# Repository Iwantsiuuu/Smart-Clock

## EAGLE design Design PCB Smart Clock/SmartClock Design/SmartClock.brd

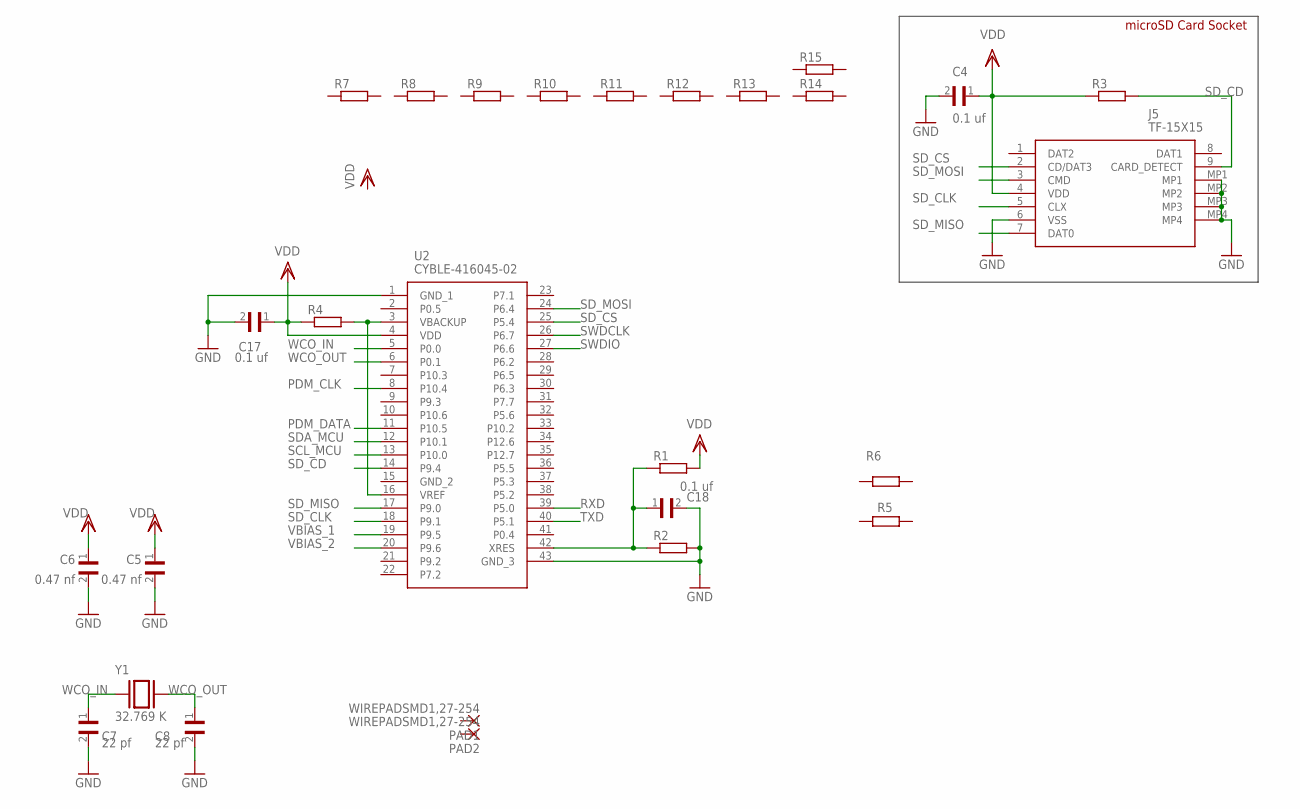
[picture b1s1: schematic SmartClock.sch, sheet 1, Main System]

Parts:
C4, C17, C18: 0.1 uf; CAPC1608X90
C5, C6: 0.47 nf; CAPC1608X90
C7, C8: 22 pf; CAPC1608X90
J5: TF-15X15; TF15X15
PAD1, PAD2: WIREPADSMD1,27-254; SMD1,27-2,54
R1, R2, R3, R4, R5, R6, R7, R8, R9, R10, R11, R12, R13, R14, R15: R-EU_R0603; R0603
U2: CYBLE-416045-02; CYBLE41604502
Y1: 32.769 K; XTAL_MS3V-T1R

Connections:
GND: C4.2, C5.2, C6.2, C7.2, C8.2, C17.2, C18.2, J5.6 (VSS), J5.MP1, J5.MP2, J5.MP3, J5.MP4, R2.2, U2.1 (GND_1), U2.43 (GND_3)
unnamed: R4.2, U2.3 (VBACKUP), U2.16 (VREF)
unnamed: C18.1, R1.1, R2.1, U2.42 (XRES)
PDM_CLK: U2.8 (P10.4)
PDM_DATA: U2.11 (P10.5)
RXD: U2.39 (P5.0)
SCL_MCU: U2.13 (P10.0)
SDA_MCU: U2.12 (P10.1)
SD_CD: J5.9 (CARD_DETECT), R3.2, U2.14 (P9.4)
SD_CLK: J5.5 (CLX), U2.18 (P9.1)
SD_CS: J5.2 (CD/DAT3), U2.25 (P5.4)
SD_MISO: J5.7 (DAT0), U2.17 (P9.0)
SD_MOSI: J5.3 (CMD), U2.24 (P6.4)
SWDCLK: U2.26 (P6.7)
SWDIO: U2.27 (P6.6)
TXD: U2.40 (P5.1)
VBIAS_1: U2.19 (P9.5)
VBIAS_2: U2.20 (P9.6)
VDD: C4.1, C5.1, C6.1, C17.1, J5.4 (VDD), R1.2, R3.1, R4.1, U2.4 (VDD)
WCO_IN: C7.1, U2.5 (P0.0), Y1.1
WCO_OUT: C8.1, U2.6 (P0.1), Y1.2

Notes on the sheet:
microSD Card Socket

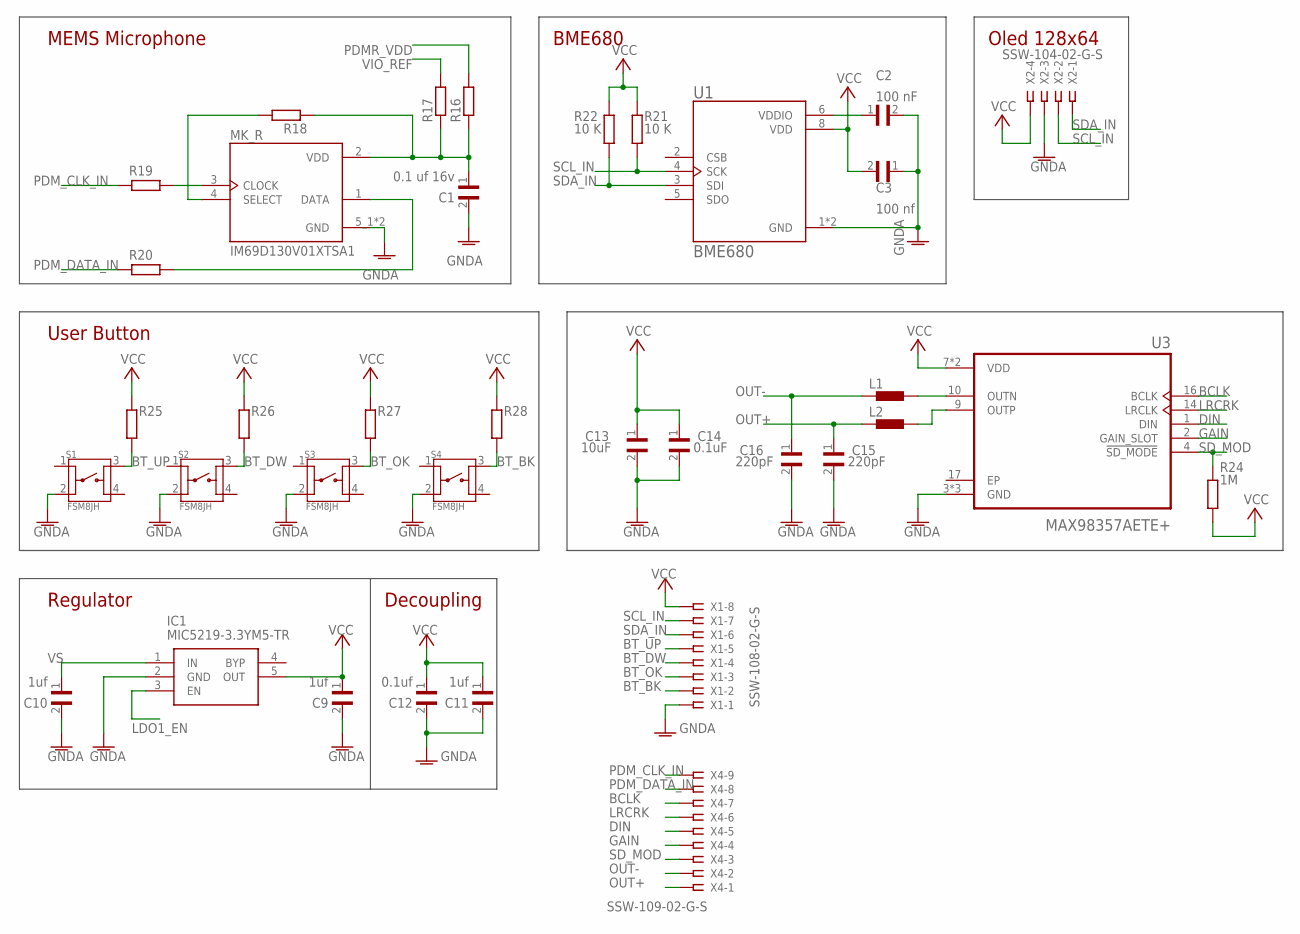
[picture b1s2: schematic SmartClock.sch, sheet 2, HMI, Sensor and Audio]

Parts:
C1: 0.1 uf 16v; CAPC1608X90
C2: 100 nF; CAPC1608X90
C3: 100 nf; CAPC1608X90
C9, C10, C11: 1uf; CAPC1608X90
C12: 0.1uf; CAPC1608X90
C13: 10uF; CAPC1608X90
C14: 0.1uF; CAPC1608X90
C15, C16: 220pF; CAPC1608X90
IC1: MIC5219-3.3YM5-TR; SOT95P280X145-5N
L1, L2: BLM15HB121SN1; 0402
MK_R: IM69D130V01XTSA1; MIC_IM69D130V01XTSA1
R16, R17, R18, R19, R20, R25, R26, R27, R28: R-EU_R0603; R0603
R21, R22: 10 K; R0603
R24: 1M; R0603
S1, S2, S3, S4: FSM8JH; SW_FSM8JH
U1: BME680; PSON80P300X300X100-8N
U3: MAX98357AETE+; QFN50P300X300X80-17N
X1: SSW-108-02-G-S
X2: SSW-104-02-G-S
X4: SSW-109-02-G-S

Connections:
BCLK: U3.16 (BCLK), X4.7
BT_BK: R28.2, S4.3, X1.2
BT_DW: R26.2, S2.3, X1.4
BT_OK: R27.2, S3.3, X1.3
BT_UP: R25.2, S1.3, X1.5
DIN: U3.1 (DIN), X4.5
EP: U3.17 (EP)
GAIN: U3.2 (GAIN_SLOT), X4.4
GNDA: C1.2, C2.2, C3.1, C9.2, C10.2, C11.2, C12.2, C13.2, C14.2, C15.2, C16.2, IC1.2 (GND), MK_R.5_1 (GND), MK_R.5_2 (GND), S1.2, S2.2, S3.2, S4.2, U1.1 (GND), U1.7 (GND), U3.3 (GND), U3.11 (GND), U3.15 (GND), X1.1, X2.3
LDO1_EN: IC1.3 (EN)
LRCRK: U3.14 (LRCLK), X4.6
unnamed: MK_R.3 (CLOCK), R19.1
unnamed: MK_R.4 (SELECT), R18.2
unnamed: C1.1, MK_R.2 (VDD), R16.1, R17.1, R18.1
unnamed: MK_R.1 (DATA), R20.1
unnamed: C2.1, U1.6 (VDDIO)
unnamed: L1.2, U3.10 (OUTN)
unnamed: L2.2, U3.9 (OUTP)
OUT+: C15.1, L2.1, X4.1
OUT-: C16.1, L1.1, X4.2
PDMR_VDD: R16.2
PDM_CLK_IN: R19.2, X4.9
PDM_DATA_IN: R20.2, X4.8
SCL_IN: R21.2, U1.4 (SCK), X1.7, X2.2
SDA_IN: R22.2, U1.3 (SDI), X1.6, X2.1
SD_MOD: R24.1, U3.4 (!SD_MODE), X4.3
VCC: C3.2, C9.1, C11.1, C12.1, C13.1, C14.1, IC1.5 (OUT), R21.1, R22.1, R24.2, R25.1, R26.1, R27.1, R28.1, U1.8 (VDD), U3.7 (VDD), U3.8 (VDD), X1.8, X2.4
VIO_REF: R17.2
VS: C10.1, IC1.1 (IN)

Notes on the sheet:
MEMS Microphone
BME680
Oled 128x64
User Button
Regulator
Decoupling

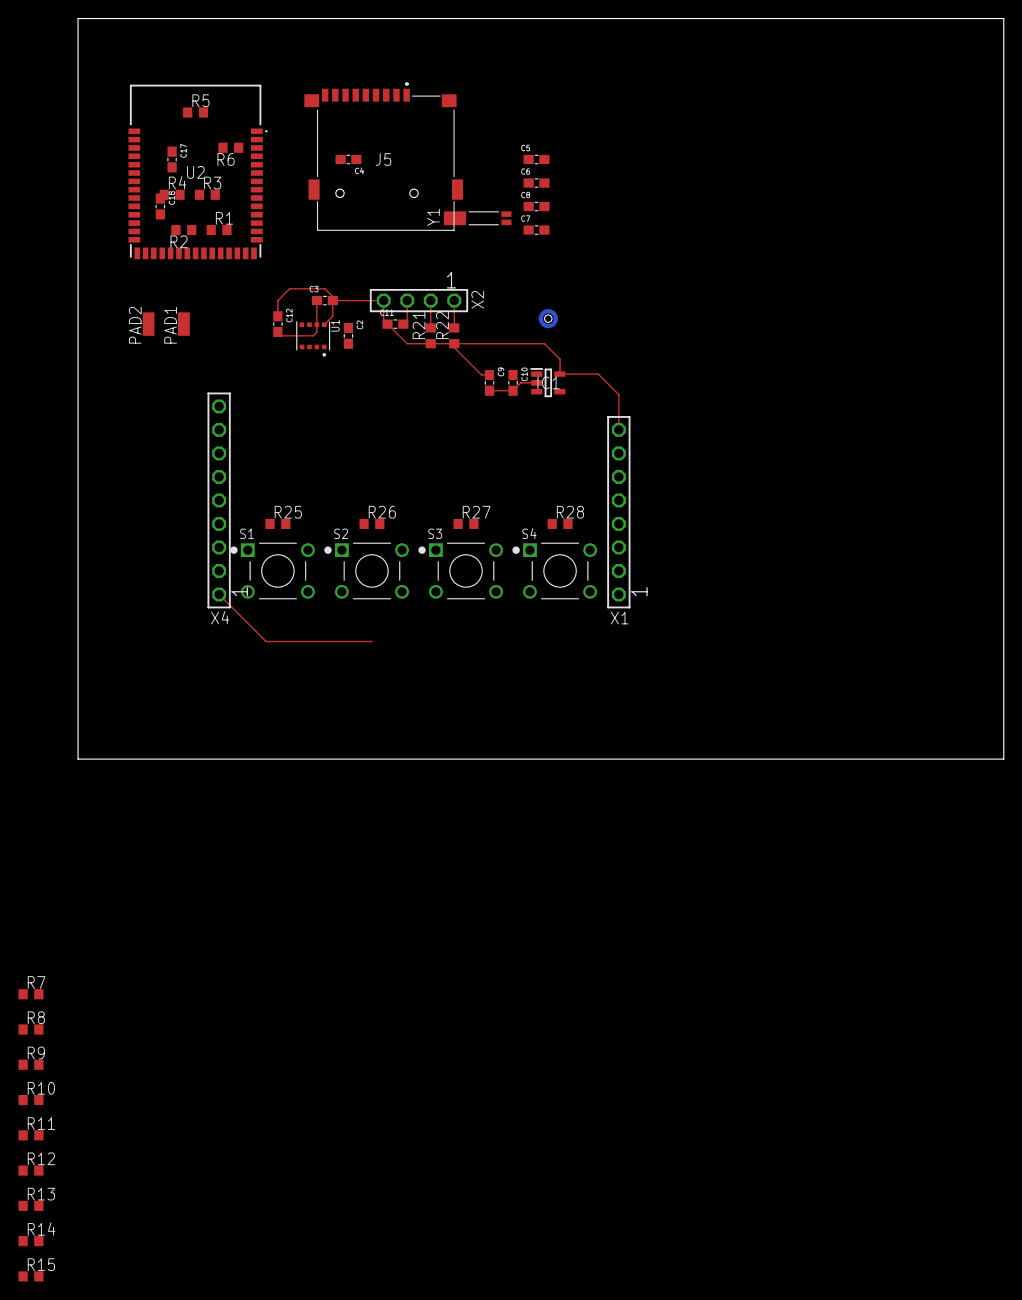
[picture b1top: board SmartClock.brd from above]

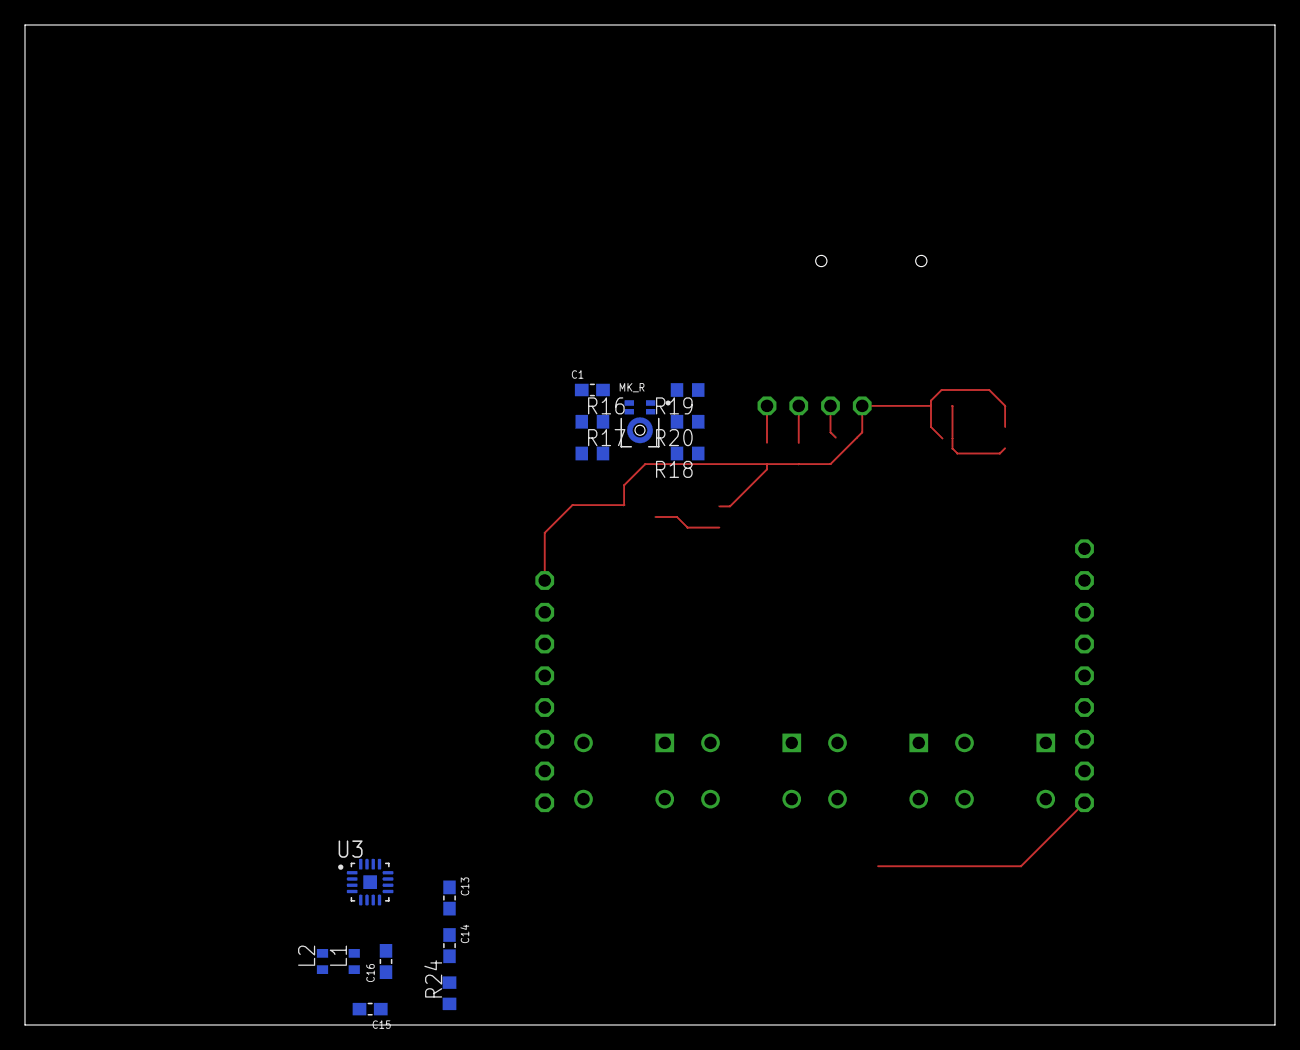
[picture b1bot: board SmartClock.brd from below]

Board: 2 copper layers, 100.0 x 80.0 mm, 63 parts (15 on the bottom side), 36 nets.

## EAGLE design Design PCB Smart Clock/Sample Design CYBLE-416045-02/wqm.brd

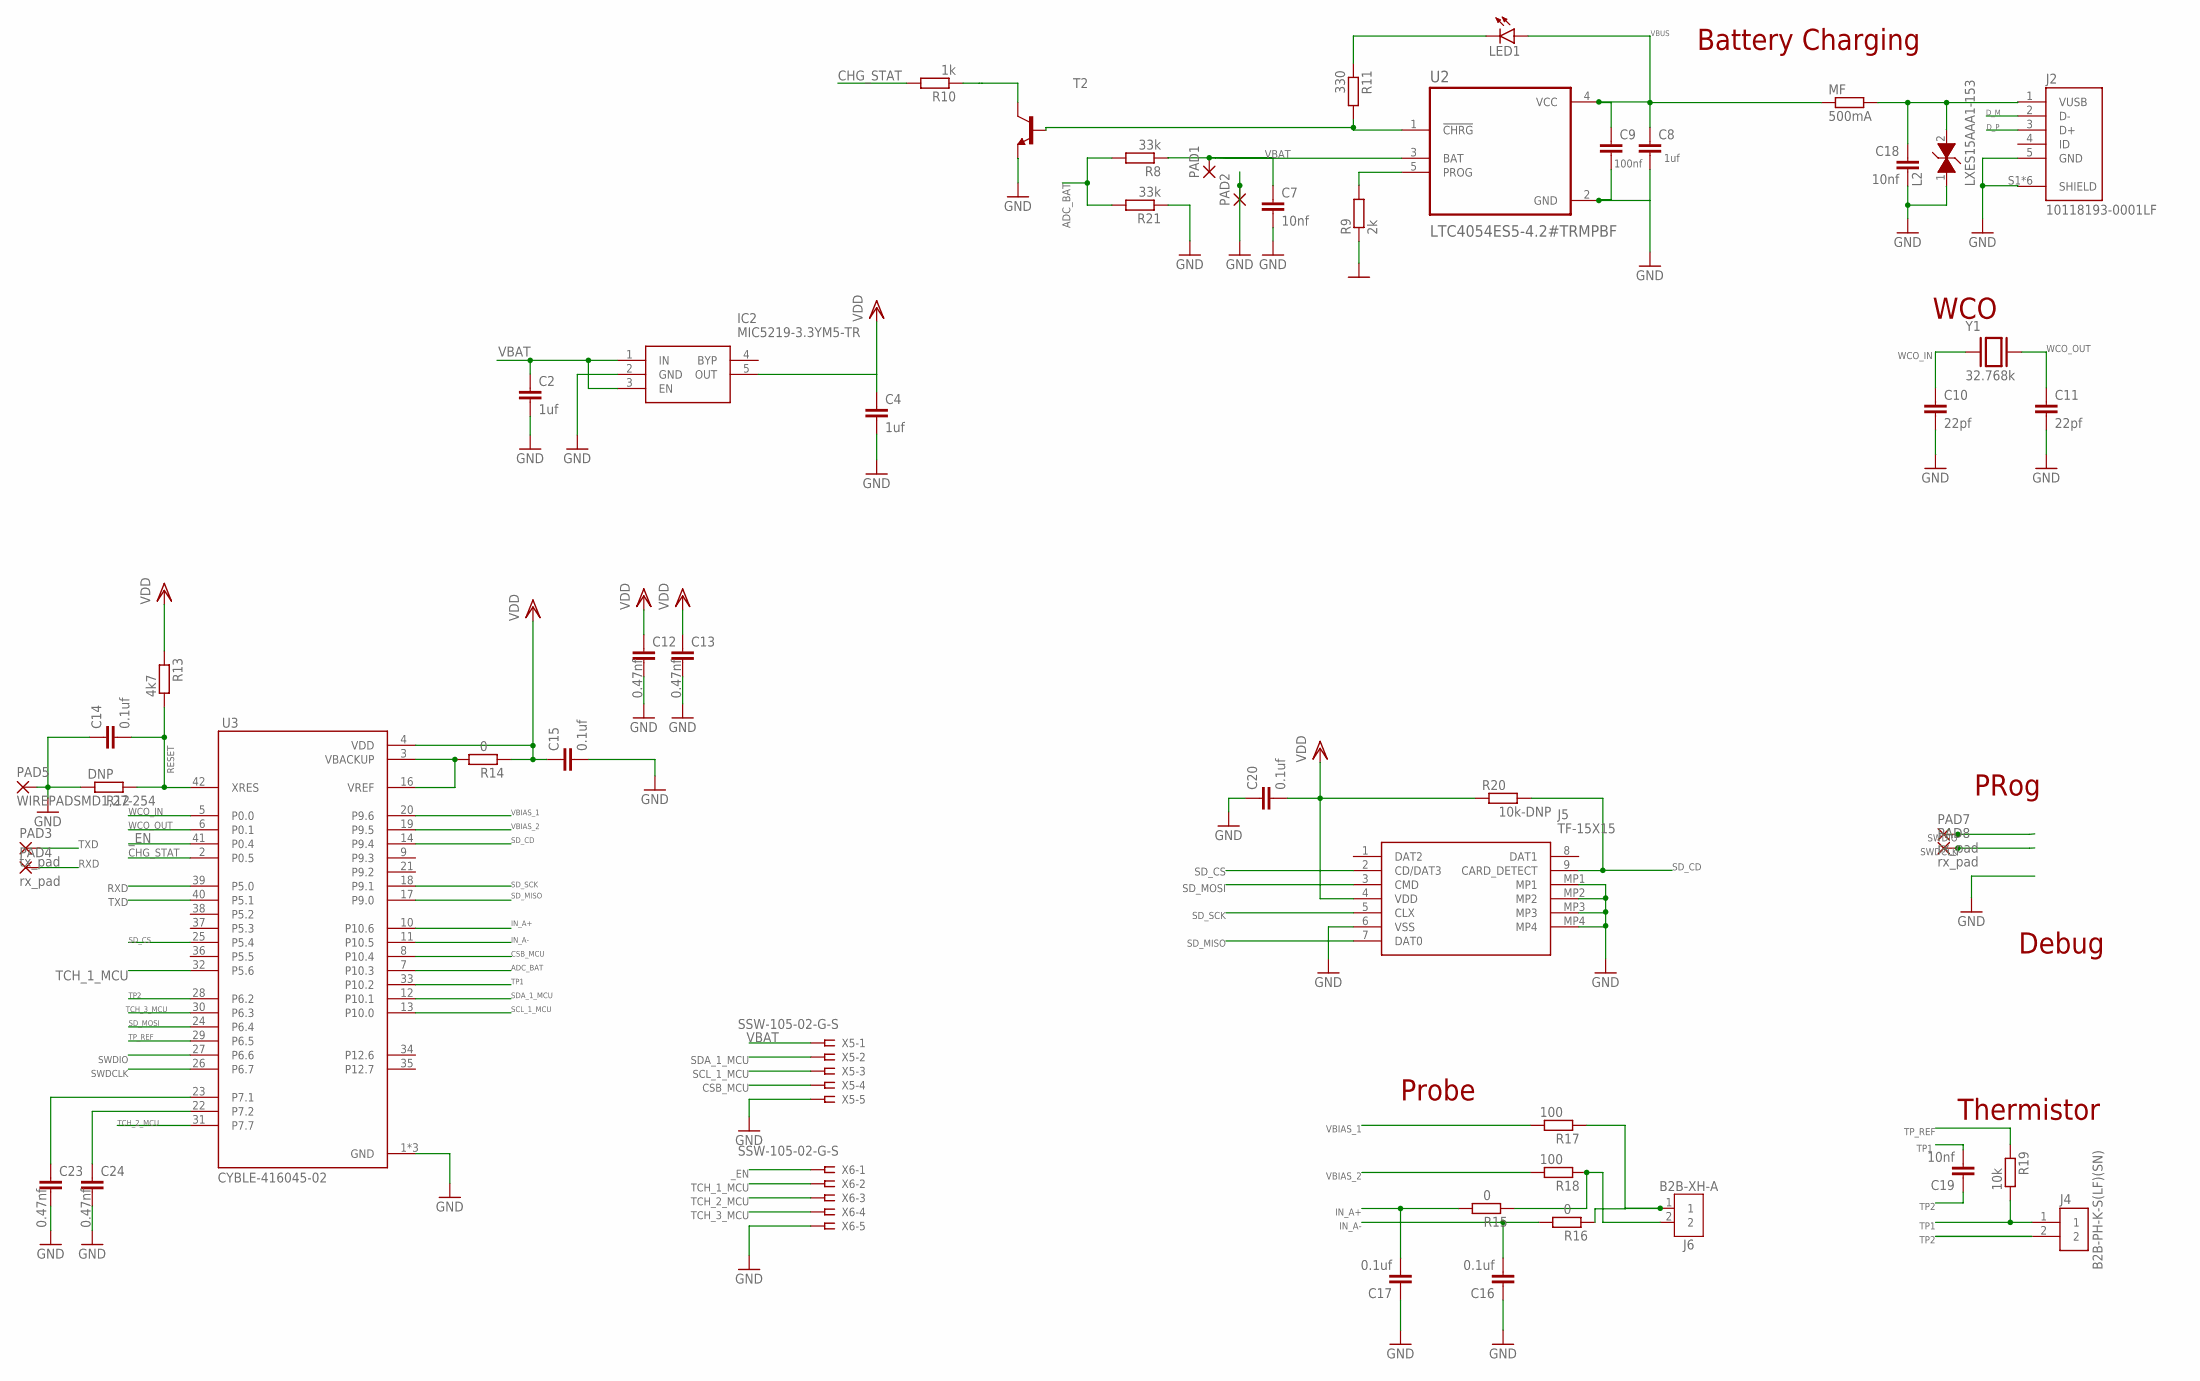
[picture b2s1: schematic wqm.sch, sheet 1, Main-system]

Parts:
C2, C4, C8: 1uf; C0603K
C7: 10nf; C0603K
C9: 100nf; C0603K
C10, C11: 22pf; C0402K
C12, C13, C23, C24: 0.47nf; C0402K
C14: 0.1uf; C0402K
C15, C16, C17, C20: 0.1uf; C0603K
C18, C19: 10nf; C0402K
IC2: MIC5219-3.3YM5-TR; SOT95P280X145-5N
J2: 10118193-0001LF; AMPHENOL_10118193-0001LF
J4: B2B-PH-K-S(LF)(SN); JST_B2B-PH-K-S(LF)(SN)
J5: TF-15X15; TF15X15
J6: B2B-XH-A
L2: LXES15AAA1-153; INDC1005X45
LED1: LEDSML0603; SML0603
MF: 500mA; R0805
PAD1, PAD2: SMD2; SMD1,27-2,54
PAD3: tx_pad; SMD1,27-2,54
PAD4, PAD7, PAD8: rx_pad; SMD1,27-2,54
PAD5: WIREPADSMD1,27-254; SMD1,27-2,54
R8, R21: 33k; R0603
R9: 2k; R0603
R10: 1k; R0603
R11: 330; R0603
R12: DNP; R0603
R13: 4k7; R0603
R14, R15, R16: 0; R0603
R17, R18: 100; R0603
R19: 10k; R0603
R20: 10k-DNP; R0603
T2: MMBT4401LT1-NPN-SOT23-BEC; SOT23-BEC
U2: LTC4054ES5-4.2#TRMPBF; SOT95P280X100-5N
U3: CYBLE-416045-02; XCVR_CYBLE-416045-02
X5, X6: SSW-105-02-G-S
Y1: 32.768k; XTAL_MS3V-T1R

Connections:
ADC_BAT: R8.2, R21.2, U3.7 (P10.3)
CHG_STAT: R10.2, U3.2 (P0.5)
CSB_MCU: U3.8 (P10.4), X5.4
D_M: J2.2 (D-)
D_P: J2.3 (D+)
GND: C2.2, C4.2, C7.2, C8.2, C9.2, C10.2, C11.2, C12.2, C13.2, C14.1, C15.2, C16.1, C17.1, C18.2, C20.1, C23.2, C24.2, IC2.2 (GND), J2.5 (GND), J2.S1 (SHIELD), J2.S2 (SHIELD), J2.S3 (SHIELD), J2.S4 (SHIELD), J2.S5 (SHIELD), J2.S6 (SHIELD), J5.6 (VSS), J5.MP1, J5.MP2, J5.MP3, J5.MP4, L2.1, PAD2.1, PAD5.1, R9.1, R12.2, R21.1, T2.E, U2.2 (GND), U3.1 (GND), U3.15 (GND), U3.43 (GND), X5.5, X6.5
IN_A+: C17.2, R15.2, U3.10 (P10.6)
IN_A-: C16.2, R16.2, U3.11 (P10.5)
unnamed: C24.1, U3.22 (P7.2)
unnamed: C18.1, J2.1 (VUSB), L2.2, MF.2
unnamed: R9.2, U2.5 (PROG)
unnamed: R10.1, T2.C
unnamed: R11.2, T2.B, U2.1 (!CHRG)
unnamed: LED1.C, R11.1
unnamed: R14.2, U3.3 (VBACKUP), U3.16 (VREF)
unnamed: J6.1, R16.1, R17.1
unnamed: J6.2, R15.1, R18.1
unnamed: C23.1, U3.23 (P7.1)
RESET: C14.2, R12.1, R13.2, U3.42 (XRES)
RXD: PAD4.1, U3.39 (P5.0)
SCL_1_MCU: U3.13 (P10.0), X5.3
SDA_1_MCU: U3.12 (P10.1), X5.2
SD_CD: J5.9 (CARD_DETECT), R20.2, U3.14 (P9.4)
SD_CS: J5.2 (CD/DAT3), U3.25 (P5.4)
SD_MISO: J5.7 (DAT0), U3.17 (P9.0)
SD_MOSI: J5.3 (CMD), U3.24 (P6.4)
SD_SCK: J5.5 (CLX), U3.18 (P9.1)
SWDCLK: PAD8.1, U3.26 (P6.7)
SWDIO: PAD7.1, U3.27 (P6.6)
TCH_1_MCU: U3.32 (P5.6), X6.2
TCH_2_MCU: U3.31 (P7.7), X6.3
TCH_3_MCU: U3.30 (P6.3), X6.4
TP1: C19.2, J4.1, R19.2, U3.33 (P10.2)
TP2: C19.1, J4.2, U3.28 (P6.2)
TP_REF: R19.1, U3.29 (P6.5)
TXD: PAD3.1, U3.40 (P5.1)
VBAT: C2.1, C7.1, IC2.1 (IN), IC2.3 (EN), PAD1.1, R8.1, U2.3 (BAT), X5.1
VBIAS_1: R17.2, U3.20 (P9.6)
VBIAS_2: R18.2, U3.19 (P9.5)
VBUS: C8.1, C9.1, LED1.A, MF.1, U2.4 (VCC)
VDD: C4.1, C12.1, C13.1, C15.1, C20.2, IC2.5 (OUT), J5.4 (VDD), R13.1, R14.1, R20.1, U3.4 (VDD)
WCO_IN: C10.1, U3.5 (P0.0), Y1.1
WCO_OUT: C11.1, U3.6 (P0.1), Y1.2
_EN: U3.41 (P0.4), X6.1

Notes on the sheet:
Battery Charging
WCO
PRog
Debug
Thermistor
Probe

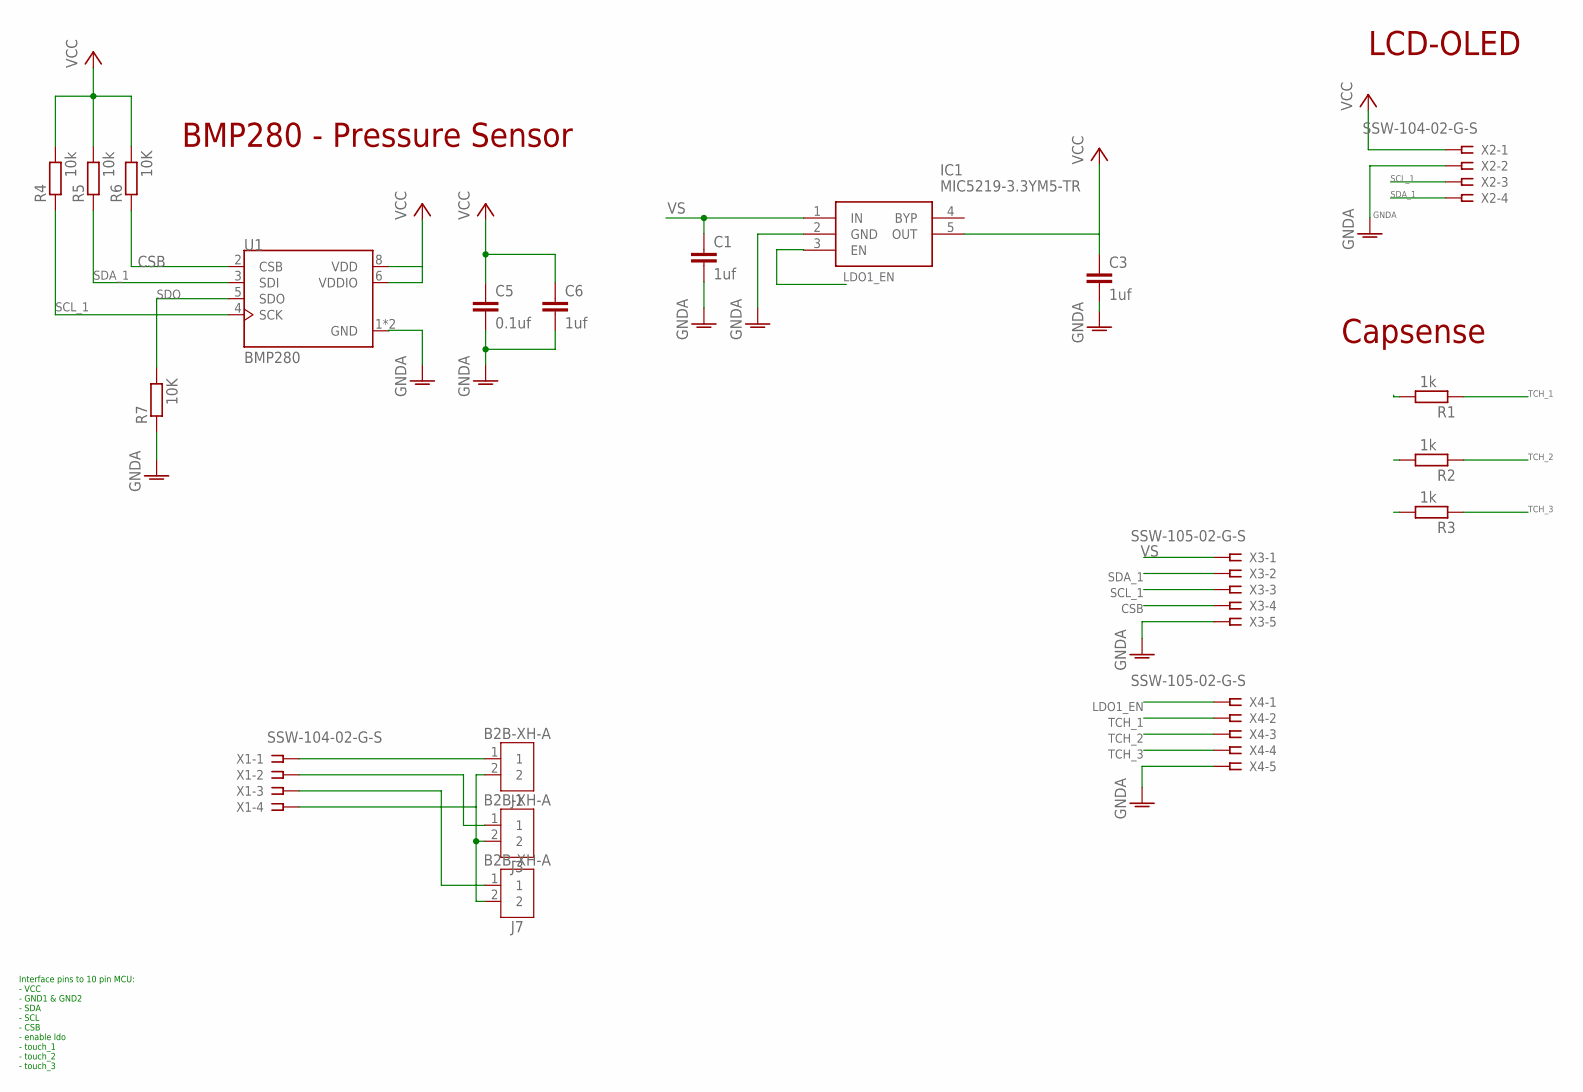
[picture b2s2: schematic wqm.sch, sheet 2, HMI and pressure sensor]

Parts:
C1, C3, C6: 1uf; C0603K
C5: 0.1uf; C0603K
IC1: MIC5219-3.3YM5-TR; SOT95P280X145-5N
J1, J3, J7: B2B-XH-A
R1, R2, R3: 1k; R0603
R4, R5: 10k; R0603
R6, R7: 10K; R0603
U1: BMP280; XDCR_BMP280
X1, X2: SSW-104-02-G-S
X3, X4: SSW-105-02-G-S

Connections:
CSB: R6.1, U1.2 (CSB), X3.4
GNDA: C1.2, C3.2, C5.2, C6.2, IC1.2 (GND), R7.1, U1.1 (GND), U1.7 (GND), X2.2, X3.5, X4.5
LDO1_EN: IC1.3 (EN), X4.1
unnamed: J1.1, X1.1
unnamed: J3.1, X1.2
unnamed: J7.1, X1.3
unnamed: J1.2, J3.2, J7.2, X1.4
SCL_1: R4.1, U1.4 (SCK), X2.3, X3.3
SDA_1: R5.1, U1.3 (SDI), X2.4, X3.2
SDO: R7.2, U1.5 (SDO)
TCH_1: R1.1, X4.2
TCH_2: R2.1, X4.3
TCH_3: R3.1, X4.4
VCC: C3.1, C5.1, C6.1, IC1.5 (OUT), R4.2, R5.2, R6.2, U1.6 (VDDIO), U1.8 (VDD), X2.1
VS: C1.1, IC1.1 (IN), X3.1

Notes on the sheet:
BMP280 - Pressure Sensor
LCD-OLED
Capsense
Interface pins to 10 pin MCU: - VCC - GND1 & GND2 - SDA - SCL - CSB - enable ldo - touch_1 - touch_2 - touch_3

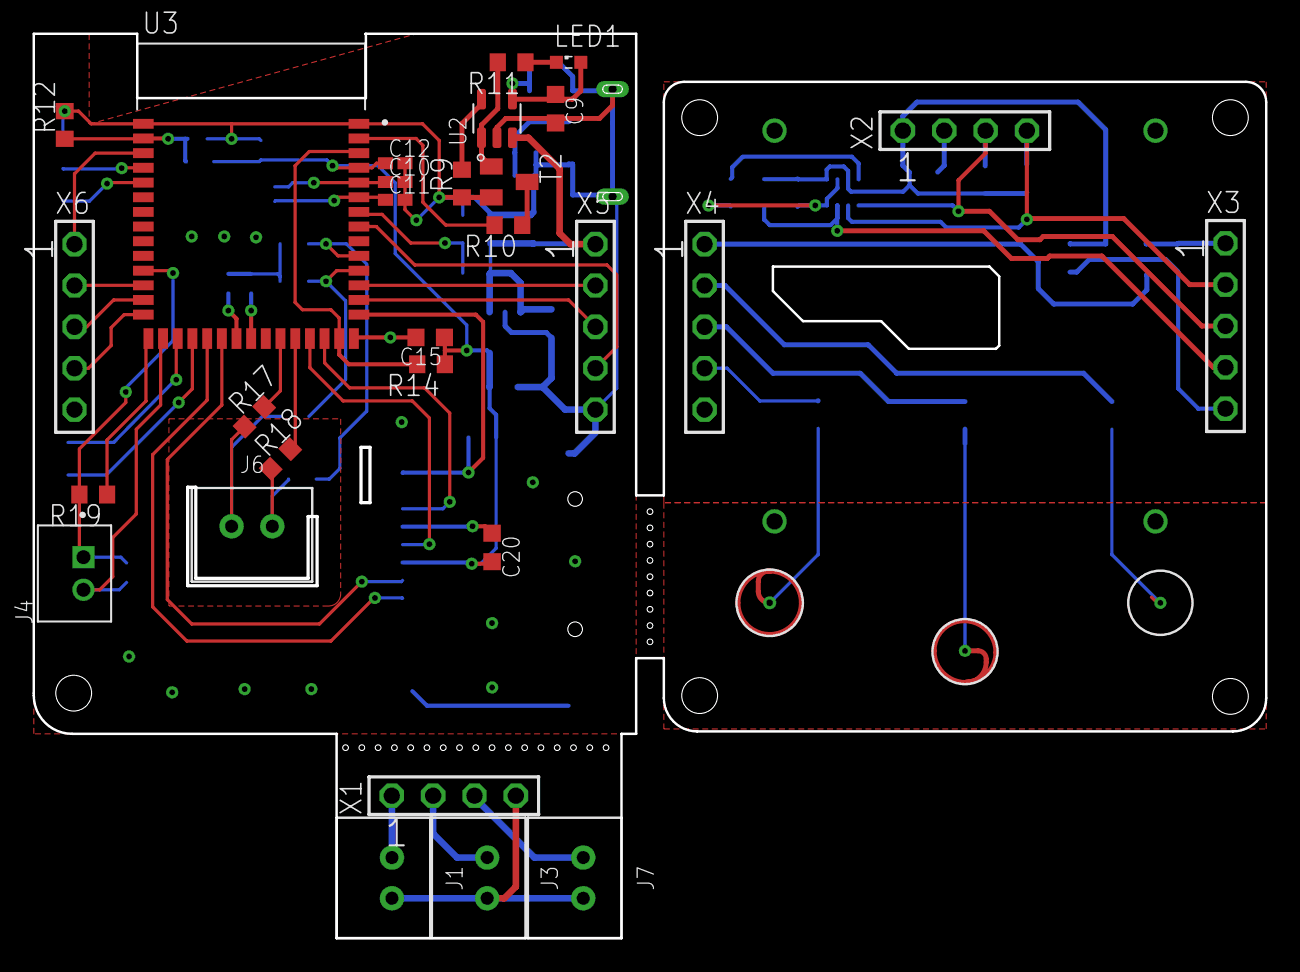
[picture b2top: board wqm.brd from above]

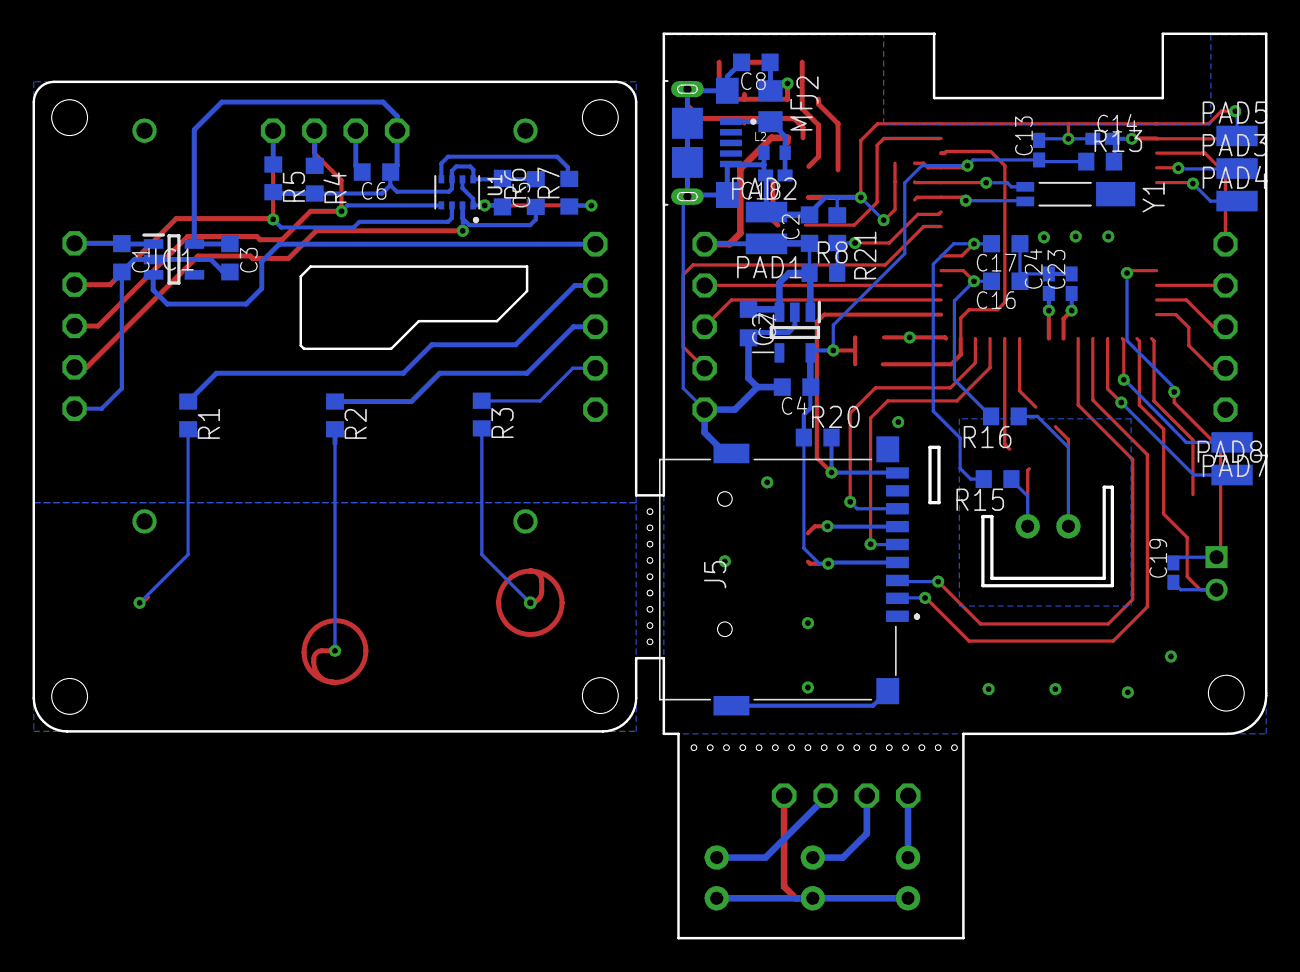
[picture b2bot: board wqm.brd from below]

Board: 2 copper layers, 75.7 x 55.5 mm, 73 parts (44 on the bottom side), 57 nets.

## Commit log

2024-01-31 Commite SmartClock
2024-01-31 Move file into folder
2024-01-31 move file
2024-02-01 Commit folder
2024-02-01 comm
2024-02-02 cmt edit
2024-02-02 New workspace
2024-02-02 Cmt RTCP_Basic
2024-02-07 update interface smart clock
2024-02-07 update task sensor and environment menu
2024-02-11 Interface u8g2 for PSoC 6
2024-02-11 edit u8g2
2024-02-19 Add PCB design and edit u8g2 interface
2024-03-08 Add RTC Setup
2024-03-08 Test
2024-03-08 Apalah
2024-04-02 update interface with RTC
2024-06-07 update Smart Clock
2024-06-12 update smart clock project workspace
2024-06-14 Update 14 june
2024-06-14 Add smart_clock_speech
